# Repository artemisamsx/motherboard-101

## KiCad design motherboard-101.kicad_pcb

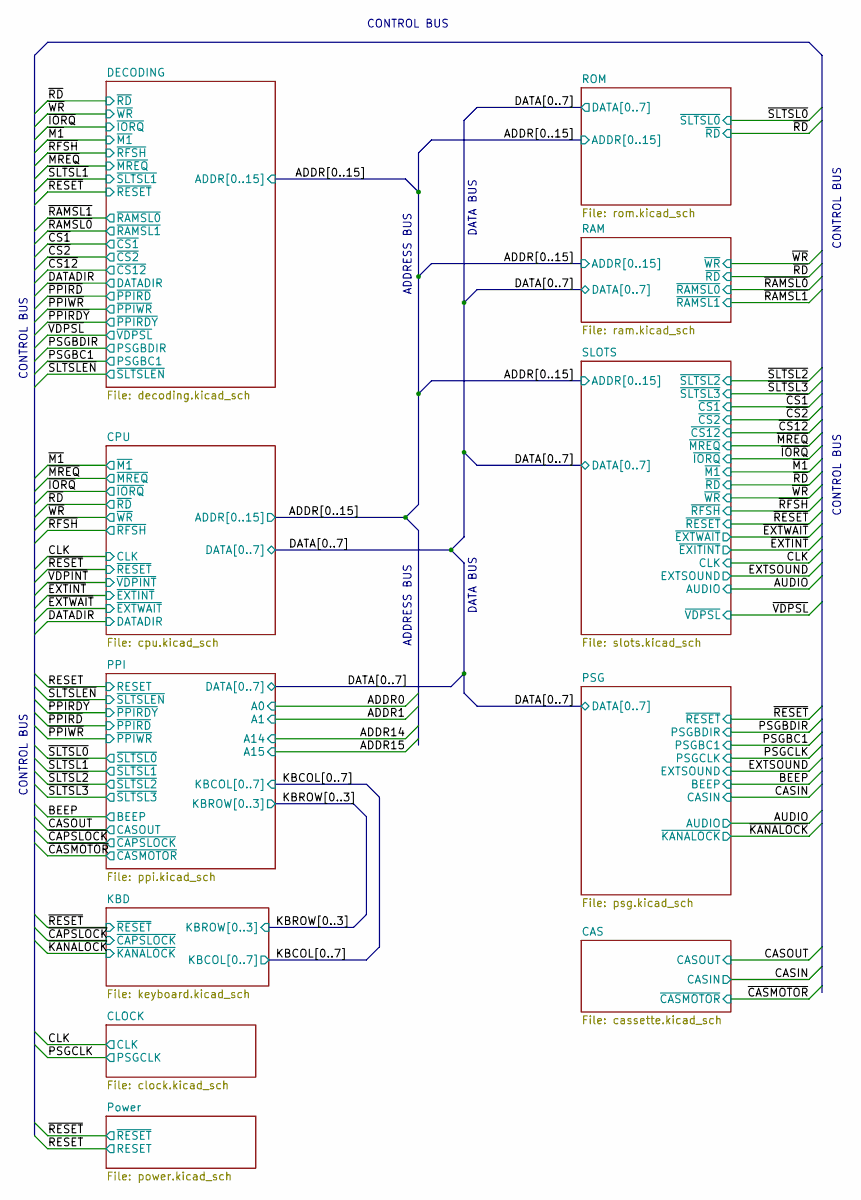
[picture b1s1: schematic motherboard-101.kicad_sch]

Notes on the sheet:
CONTROL BUS
ADDRESS BUS
DATA BUS

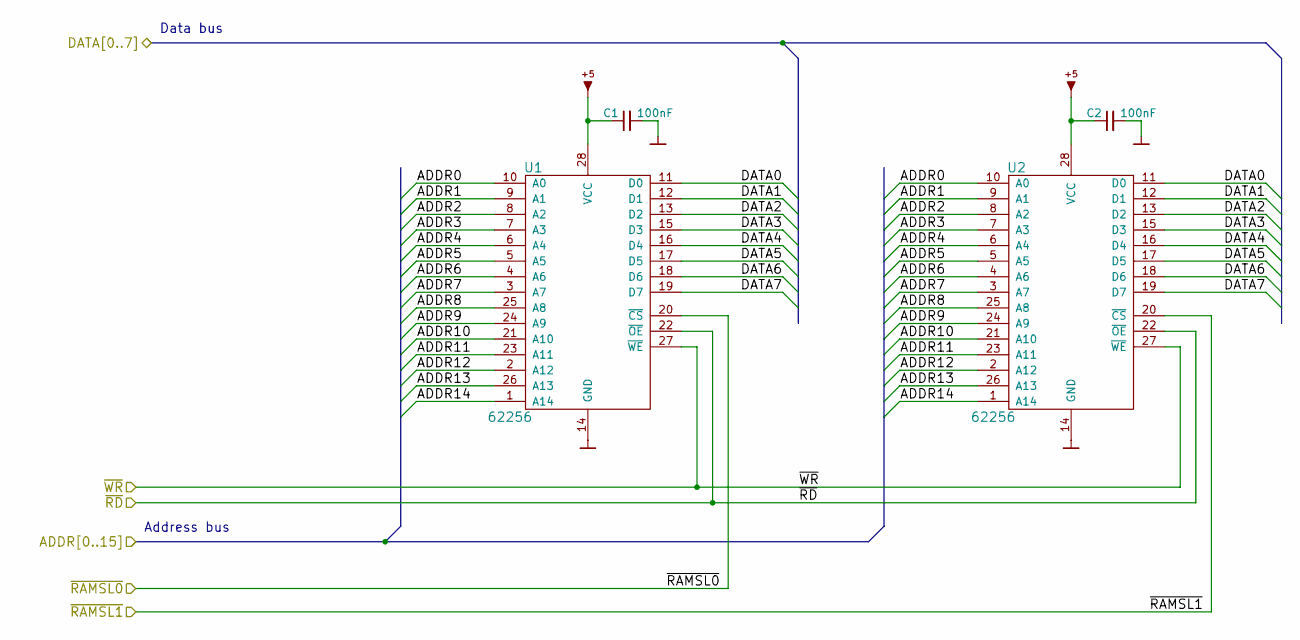
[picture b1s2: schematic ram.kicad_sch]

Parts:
C1, C2: 100nF; Disc_capacitor
U1, U2: 62256; DIP-28_600

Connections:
/ADDR0: U1.10 (A0), U2.10 (A0); also elsewhere on the board
/ADDR1: U1.9 (A1), U2.9 (A1); also elsewhere on the board
/ADDR14: U1.1 (A14), U2.1 (A14); also elsewhere on the board
/CPU/ADDR2: U1.8 (A2), U2.8 (A2); also elsewhere on the board
/CPU/ADDR3: U1.7 (A3), U2.7 (A3); also elsewhere on the board
/CPU/ADDR4: U1.6 (A4), U2.6 (A4); also elsewhere on the board
/CPU/ADDR5: U1.5 (A5), U2.5 (A5); also elsewhere on the board
/CPU/ADDR6: U1.4 (A6), U2.4 (A6); also elsewhere on the board
/CPU/ADDR7: U1.3 (A7), U2.3 (A7); also elsewhere on the board
/CPU/ADDR8: U1.25 (A8), U2.25 (A8); also elsewhere on the board
/CPU/ADDR9: U1.24 (A9), U2.24 (A9); also elsewhere on the board
/CPU/ADDR10: U1.21 (A10), U2.21 (A10); also elsewhere on the board
/CPU/ADDR11: U1.23 (A11), U2.23 (A11); also elsewhere on the board
/CPU/ADDR12: U1.2 (A12), U2.2 (A12); also elsewhere on the board
/CPU/ADDR13: U1.26 (A13), U2.26 (A13); also elsewhere on the board
/CPU/DATA0: U1.11 (D0), U2.11 (D0); also elsewhere on the board
/CPU/DATA1: U1.12 (D1), U2.12 (D1); also elsewhere on the board
/CPU/DATA2: U1.13 (D2), U2.13 (D2); also elsewhere on the board
/CPU/DATA3: U1.15 (D3), U2.15 (D3); also elsewhere on the board
/CPU/DATA4: U1.16 (D4), U2.16 (D4); also elsewhere on the board
/CPU/DATA5: U1.17 (D5), U2.17 (D5); also elsewhere on the board
/CPU/DATA6: U1.18 (D6), U2.18 (D6); also elsewhere on the board
/CPU/DATA7: U1.19 (D7), U2.19 (D7); also elsewhere on the board
/~RAMSL0: U1.20 (~CS); also elsewhere on the board
/~RAMSL1: U2.20 (~CS); also elsewhere on the board
/~RD: U1.22 (~OE), U2.22 (~OE); also elsewhere on the board
/~WR: U1.27 (~WE), U2.27 (~WE); also elsewhere on the board
GND: C1.2, C2.2, U1.14 (GND), U2.14 (GND); also elsewhere on the board
~: C1.1, C2.1, U1.28 (VCC), U2.28 (VCC); also elsewhere on the board

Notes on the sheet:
Data bus
Address bus

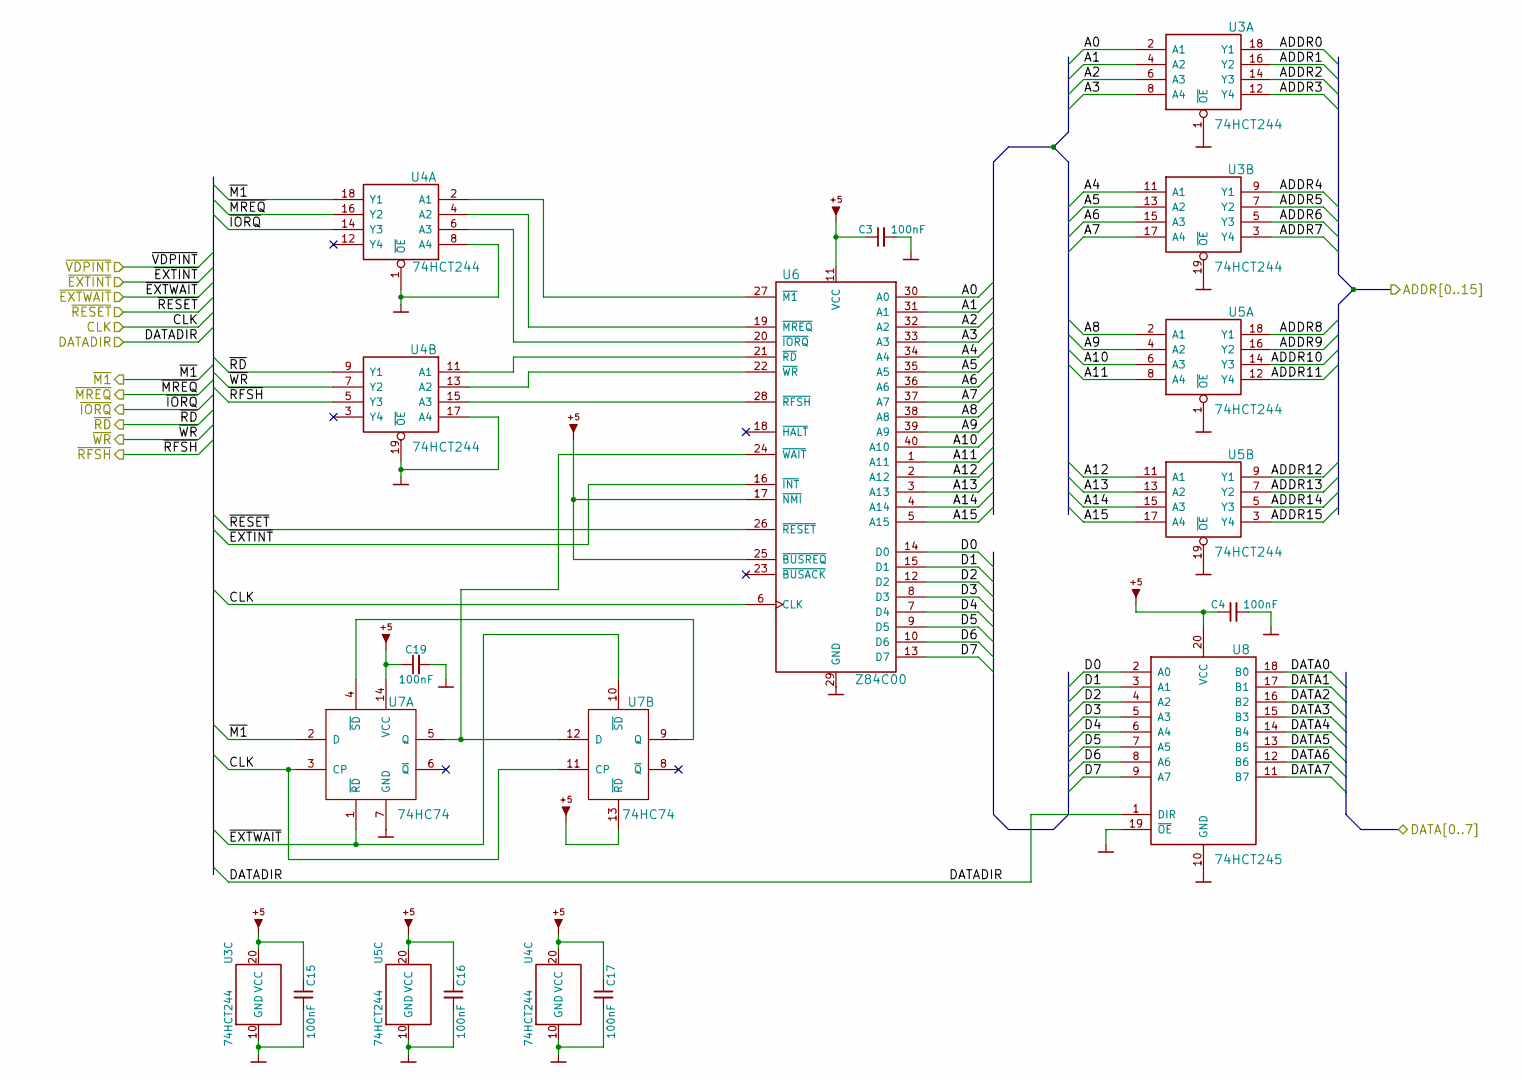
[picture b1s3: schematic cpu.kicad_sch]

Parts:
C3, C4, C15, C16, C17, C19: 100nF; Disc_capacitor
U3, U4, U5: 74HCT244; DIP-20_300
U6: Z84C00; DIP-40_600
U7: 74HC74; DIP-14_300
U8: 74HCT245; DIP-20_300

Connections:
/ADDR0: U3.18 (Y1); also elsewhere on the board
/ADDR1: U3.16 (Y2); also elsewhere on the board
/ADDR14: U5.5 (Y3); also elsewhere on the board
/ADDR15: U5.3 (Y4); also elsewhere on the board
/CLK: U6.6 (CLK), U7.3 (CP), U7.11 (CP); also elsewhere on the board
/CPU/A0: U3.2 (A1), U6.30 (A0)
/CPU/A1: U3.4 (A2), U6.31 (A1)
/CPU/A2: U3.6 (A3), U6.32 (A2)
/CPU/A3: U3.8 (A4), U6.33 (A3)
/CPU/A4: U3.11 (A1), U6.34 (A4)
/CPU/A5: U3.13 (A2), U6.35 (A5)
/CPU/A6: U3.15 (A3), U6.36 (A6)
/CPU/A7: U3.17 (A4), U6.37 (A7)
/CPU/A8: U5.2 (A1), U6.38 (A8)
/CPU/A9: U5.4 (A2), U6.39 (A9)
/CPU/A10: U5.6 (A3), U6.40 (A10)
/CPU/A11: U5.8 (A4), U6.1 (A11)
/CPU/A12: U5.11 (A1), U6.2 (A12)
/CPU/A13: U5.13 (A2), U6.3 (A13)
/CPU/A14: U5.15 (A3), U6.4 (A14)
/CPU/A15: U5.17 (A4), U6.5 (A15)
/CPU/ADDR2: U3.14 (Y3); also elsewhere on the board
/CPU/ADDR3: U3.12 (Y4); also elsewhere on the board
/CPU/ADDR4: U3.9 (Y1); also elsewhere on the board
/CPU/ADDR5: U3.7 (Y2); also elsewhere on the board
/CPU/ADDR6: U3.5 (Y3); also elsewhere on the board
/CPU/ADDR7: U3.3 (Y4); also elsewhere on the board
/CPU/ADDR8: U5.18 (Y1); also elsewhere on the board
/CPU/ADDR9: U5.16 (Y2); also elsewhere on the board
/CPU/ADDR10: U5.14 (Y3); also elsewhere on the board
/CPU/ADDR11: U5.12 (Y4); also elsewhere on the board
/CPU/ADDR12: U5.9 (Y1); also elsewhere on the board
/CPU/ADDR13: U5.7 (Y2); also elsewhere on the board
/CPU/D0: U6.14 (D0), U8.2 (A0)
/CPU/D1: U6.15 (D1), U8.3 (A1)
/CPU/D2: U6.12 (D2), U8.4 (A2)
/CPU/D3: U6.8 (D3), U8.5 (A3)
/CPU/D4: U6.7 (D4), U8.6 (A4)
/CPU/D5: U6.9 (D5), U8.7 (A5)
/CPU/D6: U6.10 (D6), U8.8 (A6)
/CPU/D7: U6.13 (D7), U8.9 (A7)
/CPU/DATA0: U8.18 (B0); also elsewhere on the board
/CPU/DATA1: U8.17 (B1); also elsewhere on the board
/CPU/DATA2: U8.16 (B2); also elsewhere on the board
/CPU/DATA3: U8.15 (B3); also elsewhere on the board
/CPU/DATA4: U8.14 (B4); also elsewhere on the board
/CPU/DATA5: U8.13 (B5); also elsewhere on the board
/CPU/DATA6: U8.12 (B6); also elsewhere on the board
/CPU/DATA7: U8.11 (B7); also elsewhere on the board
/DATADIR: U8.1 (DIR); also elsewhere on the board
/~EXTINT: U6.16 (~INT); also elsewhere on the board
/~EXTWAIT: U7.1 (~RD), U7.10 (~SD); also elsewhere on the board
/~IORQ: U4.14 (Y3); also elsewhere on the board
/~M1: U4.18 (Y1), U7.2 (D); also elsewhere on the board
/~MREQ: U4.16 (Y2); also elsewhere on the board
/~RD: U4.9 (Y1); also elsewhere on the board
/~RESET: U6.26 (~RESET); also elsewhere on the board
/~RFSH: U4.5 (Y3); also elsewhere on the board
/~WR: U4.7 (Y2); also elsewhere on the board
GND: C3.2, C4.2, C15.2, C16.2, C17.2, C19.2, U3.1 (~OE), U3.10 (GND), U3.19 (~OE), U4.1 (~OE), U4.8 (A4), U4.10 (GND), U4.17 (A4), U4.19 (~OE), U5.1 (~OE), U5.10 (GND), U5.19 (~OE), U6.29 (GND), U7.7 (GND), U8.10 (GND), U8.19 (~OE); also elsewhere on the board
unnamed: U4.2 (A1), U6.27 (~M1)
unnamed: U4.4 (A2), U6.19 (~MREQ)
unnamed: U4.6 (A3), U6.20 (~IORQ)
unnamed: U4.11 (A1), U6.21 (~RD)
unnamed: U4.13 (A2), U6.22 (~WR)
unnamed: U4.15 (A3), U6.28 (~RFSH)
unnamed: U6.24 (~WAIT), U7.5 (Q), U7.12 (D)
unnamed: U7.4 (~SD), U7.9 (Q)
~: C3.1, C4.1, C15.1, C16.1, C17.1, C19.1, U3.20 (VCC), U4.20 (VCC), U5.20 (VCC), U6.11 (VCC), U6.17 (~NMI), U6.25 (~BUSREQ), U7.13 (~RD), U7.14 (VCC), U8.20 (VCC); also elsewhere on the board

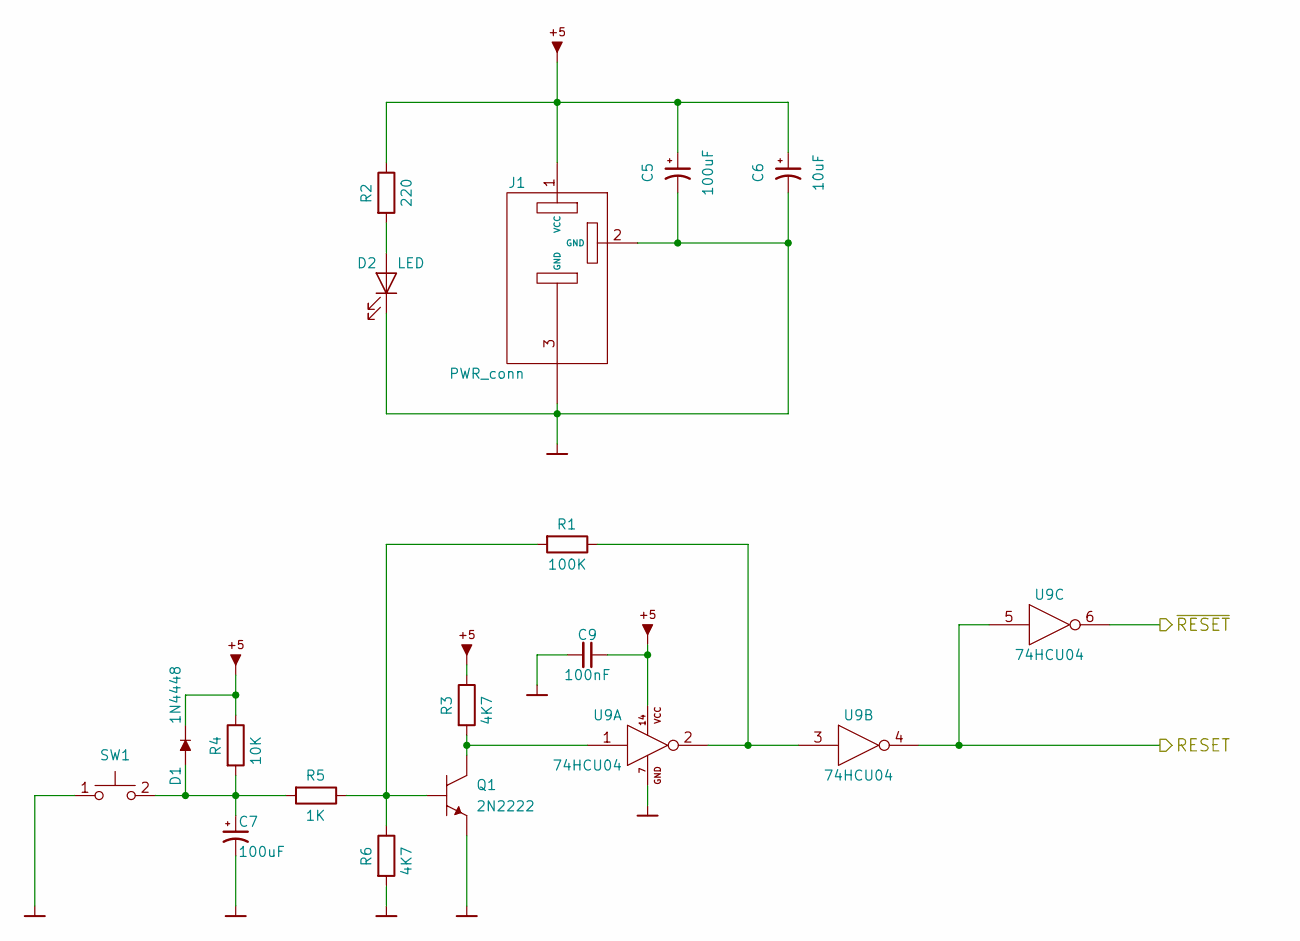
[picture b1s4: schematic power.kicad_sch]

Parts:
C5, C7: 100uF; Radial_capacitor
C6: 10uF; Radial_capacitor
C9: 100nF; Disc_capacitor
D1: 1N4448; Axial_diode
D2: LED
J1: PWR_conn; Jack_55_21
Q1: 2N2222; TO92
R1: 100K; Axial_resistor
R2: 220; Axial_resistor
R3, R6: 4K7; Axial_resistor
R4: 10K; Axial_resistor
R5: 1K; Axial_resistor
SW1: Push_button; Push_button_angled
U9: 74HCU04; DIP-14_300

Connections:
/RESET: U9.4, U9.5; also elsewhere on the board
/~RESET: U9.6; also elsewhere on the board
GND: C5.2, C6.2, C7.2, C9.2, D2.2 (K), J1.2 (GND), J1.3 (GND), Q1.3 (E), R6.2, SW1.1, U9.7 (GND); also elsewhere on the board
unnamed: C7.1, D1.1, R4.2, R5.2, SW1.2
unnamed: D2.1 (A), R2.2
unnamed: Q1.1 (1C), R3.2, U9.1
unnamed: Q1.2 (B), R1.2, R5.1, R6.1
unnamed: R1.1, U9.2, U9.3
~: C5.1, C6.1, C9.1, D1.2, J1.1 (VCC), R2.1, R3.1, R4.1, U9.14 (VCC); also elsewhere on the board

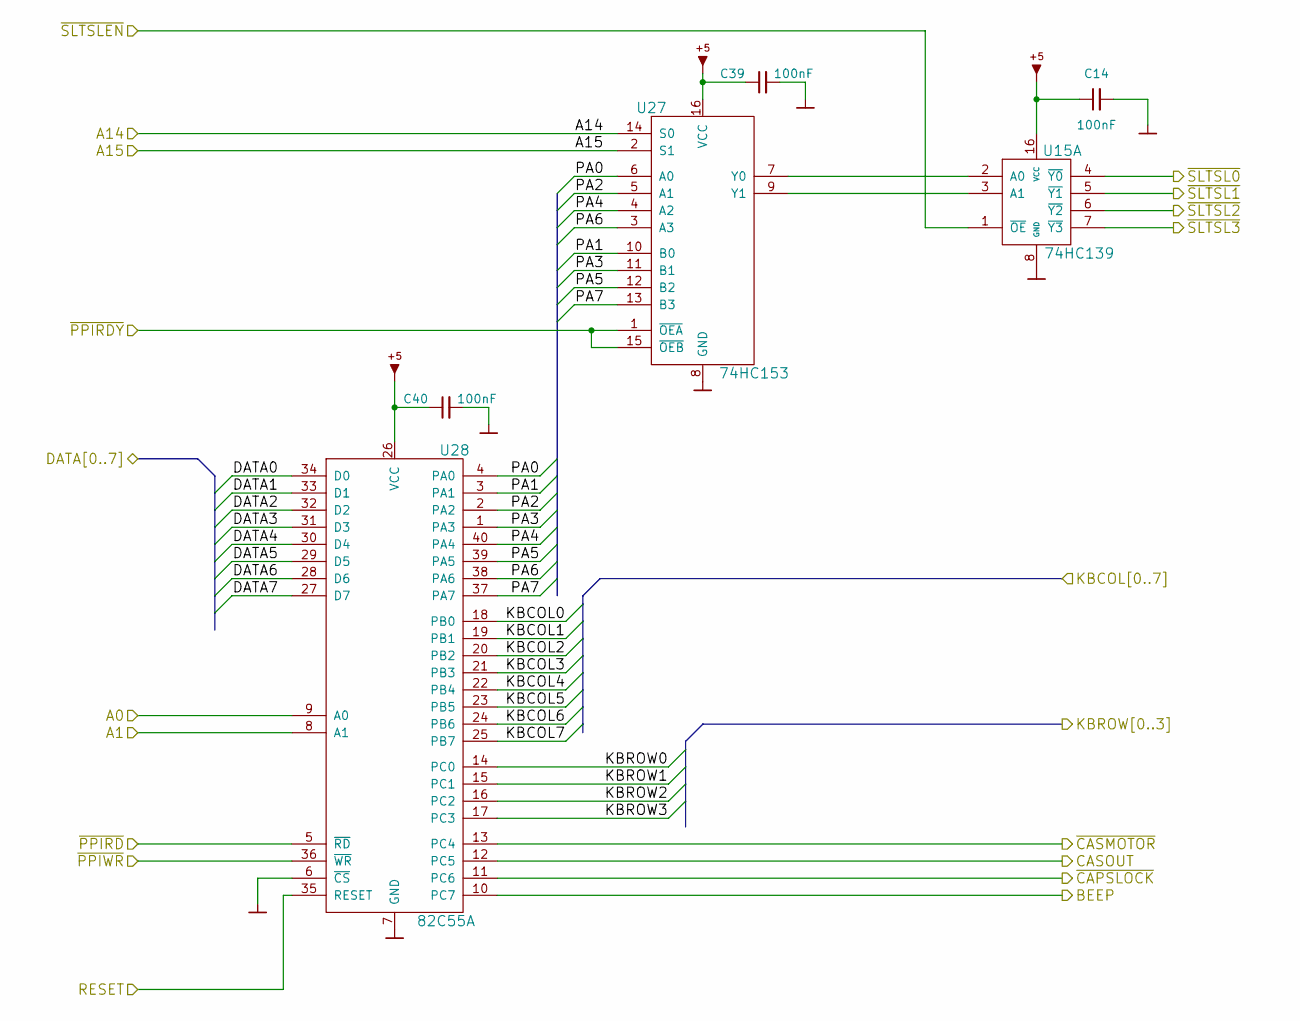
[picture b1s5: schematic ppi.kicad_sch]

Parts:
C14, C39, C40: 100nF; Disc_capacitor
U15: 74HC139; DIP-16_300
U27: 74HC153; DIP-16_300
U28: 82C55A; DIP-40_600

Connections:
/ADDR0: U28.9 (A0); also elsewhere on the board
/ADDR1: U28.8 (A1); also elsewhere on the board
/ADDR14: U27.14 (S0); also elsewhere on the board
/ADDR15: U27.2 (S1); also elsewhere on the board
/BEEP: U28.10 (PC7); also elsewhere on the board
/CASOUT: U28.12 (PC5); also elsewhere on the board
/CPU/DATA0: U28.34 (D0); also elsewhere on the board
/CPU/DATA1: U28.33 (D1); also elsewhere on the board
/CPU/DATA2: U28.32 (D2); also elsewhere on the board
/CPU/DATA3: U28.31 (D3); also elsewhere on the board
/CPU/DATA4: U28.30 (D4); also elsewhere on the board
/CPU/DATA5: U28.29 (D5); also elsewhere on the board
/CPU/DATA6: U28.28 (D6); also elsewhere on the board
/CPU/DATA7: U28.27 (D7); also elsewhere on the board
/KBD/KBCOL0: U28.18 (PB0); also elsewhere on the board
/KBD/KBCOL1: U28.19 (PB1); also elsewhere on the board
/KBD/KBCOL2: U28.20 (PB2); also elsewhere on the board
/KBD/KBCOL3: U28.21 (PB3); also elsewhere on the board
/KBD/KBCOL4: U28.22 (PB4); also elsewhere on the board
/KBD/KBCOL5: U28.23 (PB5); also elsewhere on the board
/KBD/KBCOL6: U28.24 (PB6); also elsewhere on the board
/KBD/KBCOL7: U28.25 (PB7); also elsewhere on the board
/KBD/KBROW0: U28.14 (PC0); also elsewhere on the board
/KBD/KBROW1: U28.15 (PC1); also elsewhere on the board
/KBD/KBROW2: U28.16 (PC2); also elsewhere on the board
/KBD/KBROW3: U28.17 (PC3); also elsewhere on the board
/PPI/PA0: U27.6 (A0), U28.4 (PA0)
/PPI/PA1: U27.10 (B0), U28.3 (PA1)
/PPI/PA2: U27.5 (A1), U28.2 (PA2)
/PPI/PA3: U27.11 (B1), U28.1 (PA3)
/PPI/PA4: U27.4 (A2), U28.40 (PA4)
/PPI/PA5: U27.12 (B2), U28.39 (PA5)
/PPI/PA6: U27.3 (A3), U28.38 (PA6)
/PPI/PA7: U27.13 (B3), U28.37 (PA7)
/RESET: U28.35 (RESET); also elsewhere on the board
/~CAPSLOCK: U28.11 (PC6); also elsewhere on the board
/~CASMOTOR: U28.13 (PC4); also elsewhere on the board
/~PPIRD: U28.5 (~RD); also elsewhere on the board
/~PPIRDY: U27.1 (~OEA), U27.15 (~OEB); also elsewhere on the board
/~PPIWR: U28.36 (~WR); also elsewhere on the board
/~SLTSL0: U15.4 (~Y0); also elsewhere on the board
/~SLTSL1: U15.5 (~Y1); also elsewhere on the board
/~SLTSL2: U15.6 (~Y2); also elsewhere on the board
/~SLTSL3: U15.7 (~Y3); also elsewhere on the board
/~SLTSLEN: U15.1 (~OE); also elsewhere on the board
GND: C14.2, C39.2, C40.2, U15.8 (GND), U27.8 (GND), U28.6 (~CS), U28.7 (GND); also elsewhere on the board
unnamed: U15.2 (A0), U27.7 (Y0)
unnamed: U15.3 (A1), U27.9 (Y1)
~: C14.1, C39.1, C40.1, U15.16 (VCC), U27.16 (VCC), U28.26 (VCC); also elsewhere on the board

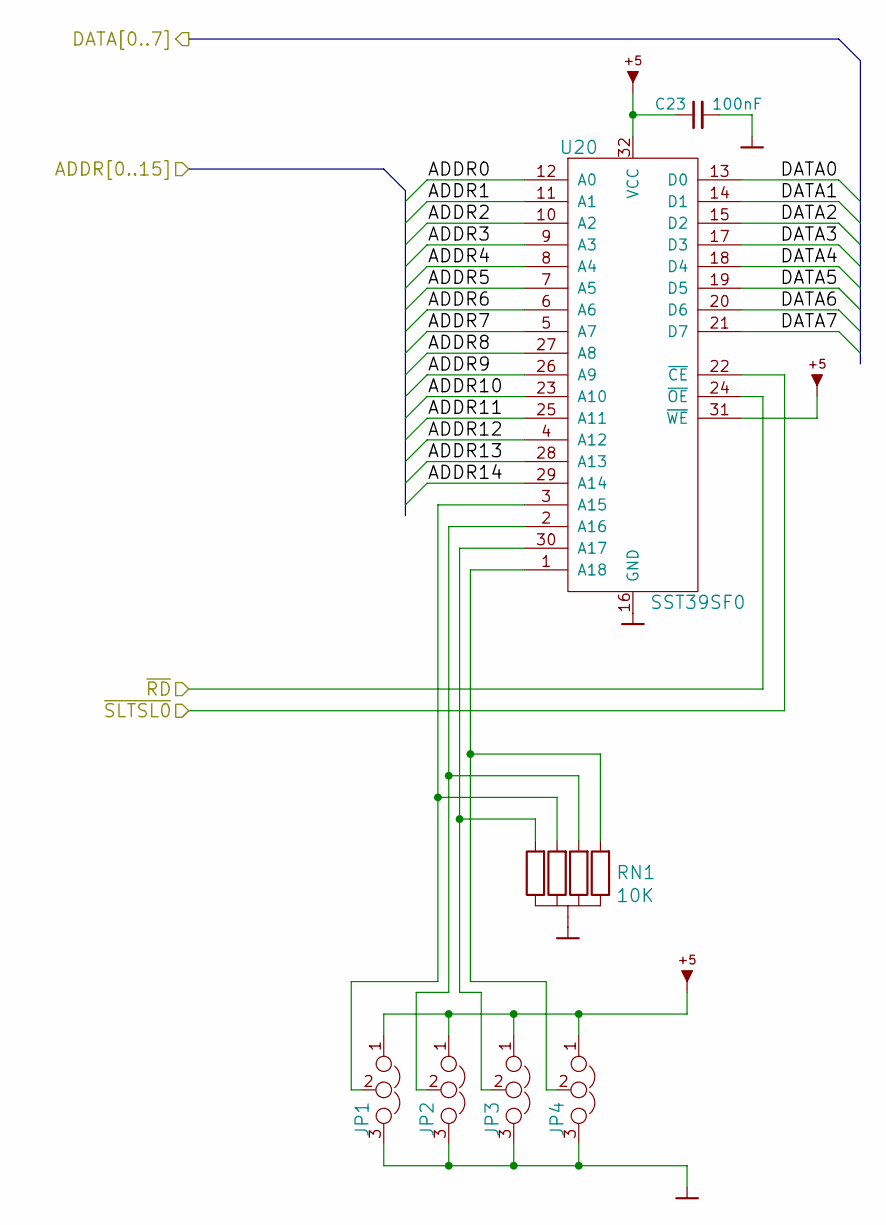
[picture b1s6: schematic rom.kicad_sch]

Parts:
C23: 100nF; Disc_capacitor
JP1, JP2, JP3, JP4: Jumper
RN1: 10K; RN4
U20: SST39SF0; DIP-32_600

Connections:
/ADDR0: U20.12 (A0); also elsewhere on the board
/ADDR1: U20.11 (A1); also elsewhere on the board
/ADDR14: U20.29 (A14); also elsewhere on the board
/CPU/ADDR2: U20.10 (A2); also elsewhere on the board
/CPU/ADDR3: U20.9 (A3); also elsewhere on the board
/CPU/ADDR4: U20.8 (A4); also elsewhere on the board
/CPU/ADDR5: U20.7 (A5); also elsewhere on the board
/CPU/ADDR6: U20.6 (A6); also elsewhere on the board
/CPU/ADDR7: U20.5 (A7); also elsewhere on the board
/CPU/ADDR8: U20.27 (A8); also elsewhere on the board
/CPU/ADDR9: U20.26 (A9); also elsewhere on the board
/CPU/ADDR10: U20.23 (A10); also elsewhere on the board
/CPU/ADDR11: U20.25 (A11); also elsewhere on the board
/CPU/ADDR12: U20.4 (A12); also elsewhere on the board
/CPU/ADDR13: U20.28 (A13); also elsewhere on the board
/CPU/DATA0: U20.13 (D0); also elsewhere on the board
/CPU/DATA1: U20.14 (D1); also elsewhere on the board
/CPU/DATA2: U20.15 (D2); also elsewhere on the board
/CPU/DATA3: U20.17 (D3); also elsewhere on the board
/CPU/DATA4: U20.18 (D4); also elsewhere on the board
/CPU/DATA5: U20.19 (D5); also elsewhere on the board
/CPU/DATA6: U20.20 (D6); also elsewhere on the board
/CPU/DATA7: U20.21 (D7); also elsewhere on the board
/~RD: U20.24 (~OE); also elsewhere on the board
/~SLTSL0: U20.22 (~CE); also elsewhere on the board
GND: C23.2, JP1.3, JP2.3, JP3.3, JP4.3, RN1.1, U20.16 (GND); also elsewhere on the board
unnamed: JP1.2, RN1.4, U20.3 (A15)
unnamed: JP2.2, RN1.3, U20.2 (A16)
unnamed: JP3.2, RN1.5, U20.30 (A17)
unnamed: JP4.2, RN1.2, U20.1 (A18)
~: C23.1, JP1.1, JP2.1, JP3.1, JP4.1, U20.31 (~WE), U20.32 (VCC); also elsewhere on the board

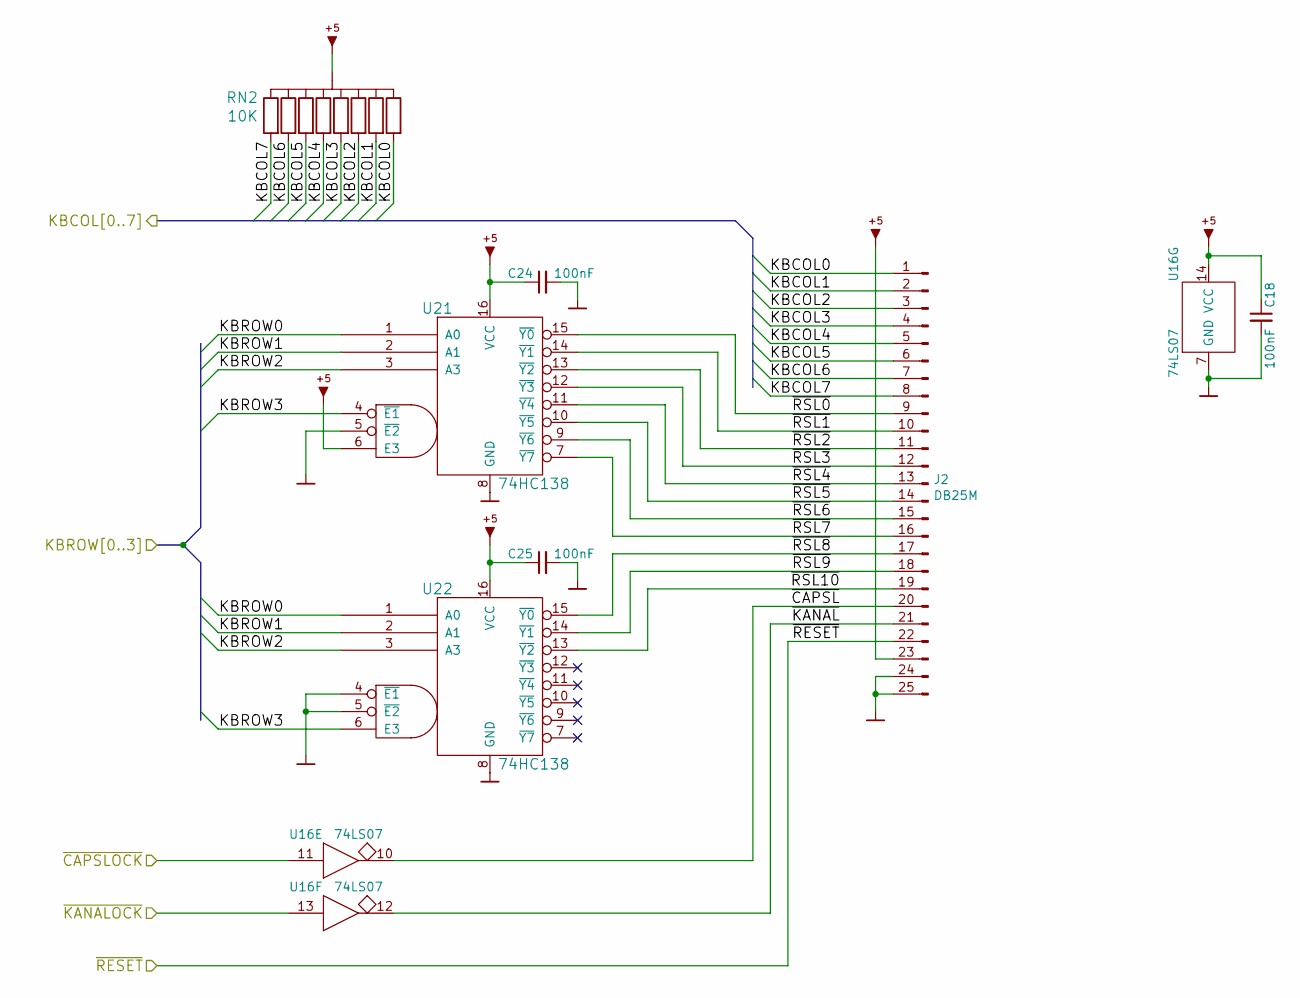
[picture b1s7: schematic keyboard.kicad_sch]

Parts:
C18, C24, C25: 100nF; Disc_capacitor
J2: DB25M
RN2: 10K; RN8
U16: 74LS07; DIP-14_300
U21, U22: 74HC138; DIP-16_300

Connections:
/KBD/KBCOL0: J2.1, RN2.2; also elsewhere on the board
/KBD/KBCOL1: J2.2, RN2.3; also elsewhere on the board
/KBD/KBCOL2: J2.3, RN2.4; also elsewhere on the board
/KBD/KBCOL3: J2.4, RN2.5; also elsewhere on the board
/KBD/KBCOL4: J2.5, RN2.6; also elsewhere on the board
/KBD/KBCOL5: J2.6, RN2.7; also elsewhere on the board
/KBD/KBCOL6: J2.7, RN2.8; also elsewhere on the board
/KBD/KBCOL7: J2.8, RN2.9; also elsewhere on the board
/KBD/KBROW0: U21.1 (A0), U22.1 (A0); also elsewhere on the board
/KBD/KBROW1: U21.2 (A1), U22.2 (A1); also elsewhere on the board
/KBD/KBROW2: U21.3 (A3), U22.3 (A3); also elsewhere on the board
/KBD/KBROW3: U21.4 (~E1), U22.6 (E3); also elsewhere on the board
/KBD/~CAPSL: J2.20, U16.10
/KBD/~KANAL: J2.21, U16.12
/KBD/~RSL0: J2.9, U21.15 (~Y0)
/KBD/~RSL1: J2.10, U21.14 (~Y1)
/KBD/~RSL2: J2.11, U21.13 (~Y2)
/KBD/~RSL3: J2.12, U21.12 (~Y3)
/KBD/~RSL4: J2.13, U21.11 (~Y4)
/KBD/~RSL5: J2.14, U21.10 (~Y5)
/KBD/~RSL6: J2.15, U21.9 (~Y6)
/KBD/~RSL7: J2.16, U21.7 (~Y7)
/KBD/~RSL8: J2.17, U22.15 (~Y0)
/KBD/~RSL9: J2.18, U22.14 (~Y1)
/KBD/~RSL10: J2.19, U22.13 (~Y2)
/~CAPSLOCK: U16.11; also elsewhere on the board
/~KANALOCK: U16.13; also elsewhere on the board
/~RESET: J2.22; also elsewhere on the board
GND: C18.2, C24.2, C25.2, J2.24, J2.25, U16.7 (GND), U21.5 (~E2), U21.8 (GND), U22.4 (~E1), U22.5 (~E2), U22.8 (GND); also elsewhere on the board
~: C18.1, C24.1, C25.1, J2.23, RN2.1, U16.14 (VCC), U21.6 (E3), U21.16 (VCC), U22.16 (VCC); also elsewhere on the board

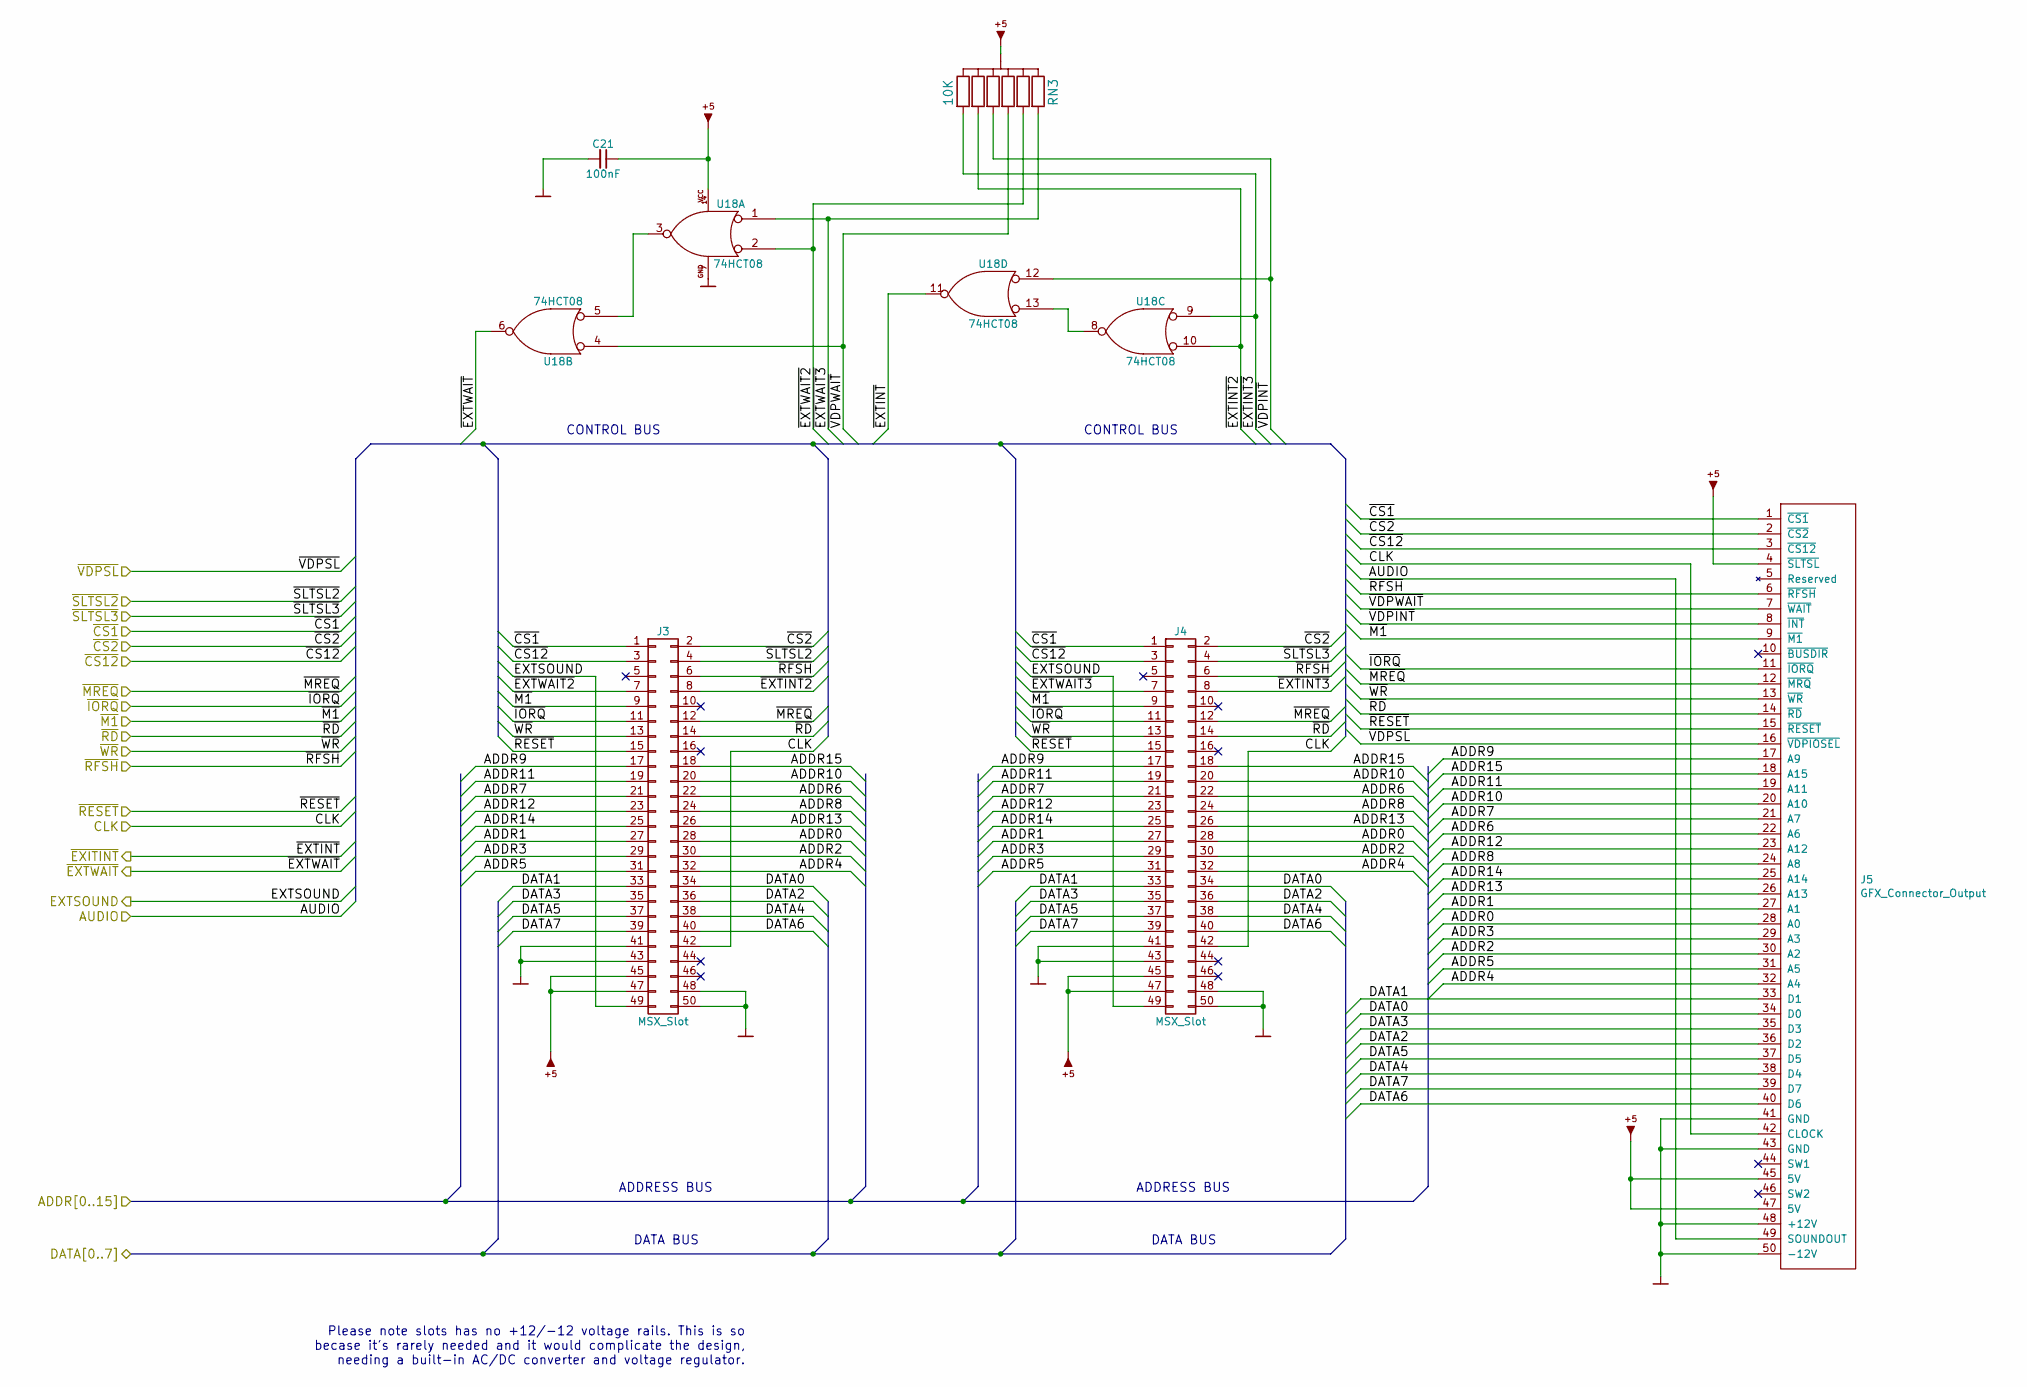
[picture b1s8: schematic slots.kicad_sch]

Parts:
C21: 100nF; Disc_capacitor
J3, J4: MSX_Slot; Slot_conn
J5: GFX_Connector_Output; GFX_conn
RN3: 10K; RN6
U18: 74HCT08; DIP-14_300

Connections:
/ADDR0: J3.28, J4.28, J5.28 (A0); also elsewhere on the board
/ADDR1: J3.27, J4.27, J5.27 (A1); also elsewhere on the board
/ADDR14: J3.25, J4.25, J5.25 (A14); also elsewhere on the board
/ADDR15: J3.18, J4.18, J5.18 (A15); also elsewhere on the board
/AUDIO: J5.49 (SOUNDOUT); also elsewhere on the board
/CLK: J3.42, J4.42, J5.42 (CLOCK); also elsewhere on the board
/CPU/ADDR2: J3.30, J4.30, J5.30 (A2); also elsewhere on the board
/CPU/ADDR3: J3.29, J4.29, J5.29 (A3); also elsewhere on the board
/CPU/ADDR4: J3.32, J4.32, J5.32 (A4); also elsewhere on the board
/CPU/ADDR5: J3.31, J4.31, J5.31 (A5); also elsewhere on the board
/CPU/ADDR6: J3.22, J4.22, J5.22 (A6); also elsewhere on the board
/CPU/ADDR7: J3.21, J4.21, J5.21 (A7); also elsewhere on the board
/CPU/ADDR8: J3.24, J4.24, J5.24 (A8); also elsewhere on the board
/CPU/ADDR9: J3.17, J4.17, J5.17 (A9); also elsewhere on the board
/CPU/ADDR10: J3.20, J4.20, J5.20 (A10); also elsewhere on the board
/CPU/ADDR11: J3.19, J4.19, J5.19 (A11); also elsewhere on the board
/CPU/ADDR12: J3.23, J4.23, J5.23 (A12); also elsewhere on the board
/CPU/ADDR13: J3.26, J4.26, J5.26 (A13); also elsewhere on the board
/CPU/DATA0: J3.34, J4.34, J5.34 (D0); also elsewhere on the board
/CPU/DATA1: J3.33, J4.33, J5.33 (D1); also elsewhere on the board
/CPU/DATA2: J3.36, J4.36, J5.36 (D2); also elsewhere on the board
/CPU/DATA3: J3.35, J4.35, J5.35 (D3); also elsewhere on the board
/CPU/DATA4: J3.38, J4.38, J5.38 (D4); also elsewhere on the board
/CPU/DATA5: J3.37, J4.37, J5.37 (D5); also elsewhere on the board
/CPU/DATA6: J3.40, J4.40, J5.40 (D6); also elsewhere on the board
/CPU/DATA7: J3.39, J4.39, J5.39 (D7); also elsewhere on the board
/EXTSOUND: J3.49, J4.49; also elsewhere on the board
/SLOTS/~EXTINT2: J3.8, RN3.3, U18.10
/SLOTS/~EXTINT3: J4.8, RN3.2, U18.9
/SLOTS/~EXTWAIT2: J3.7, RN3.6, U18.2
/SLOTS/~EXTWAIT3: J4.7, RN3.7, U18.1
/SLOTS/~VDPINT: J5.8 (~INT), RN3.4, U18.12
/SLOTS/~VDPWAIT: J5.7 (~WAIT), RN3.5, U18.4
/~CS1: J3.1, J4.1, J5.1 (~CS1); also elsewhere on the board
/~CS2: J3.2, J4.2, J5.2 (~CS2); also elsewhere on the board
/~CS12: J3.3, J4.3, J5.3 (~CS12); also elsewhere on the board
/~EXTINT: U18.11; also elsewhere on the board
/~EXTWAIT: U18.6; also elsewhere on the board
/~IORQ: J3.11, J4.11, J5.11 (~IORQ); also elsewhere on the board
/~M1: J3.9, J4.9, J5.9 (~M1); also elsewhere on the board
/~MREQ: J3.12, J4.12, J5.12 (~MRQ); also elsewhere on the board
/~RD: J3.14, J4.14, J5.14 (~RD); also elsewhere on the board
/~RESET: J3.15, J4.15, J5.15 (~RESET); also elsewhere on the board
/~RFSH: J3.6, J4.6, J5.6 (~RFSH); also elsewhere on the board
/~SLTSL2: J3.4; also elsewhere on the board
/~SLTSL3: J4.4; also elsewhere on the board
/~VDPSL: J5.16 (~VDPIOSEL); also elsewhere on the board
/~WR: J3.13, J4.13, J5.13 (~WR); also elsewhere on the board
GND: C21.2, J3.41, J3.43, J3.48, J3.50, J4.41, J4.43, J4.48, J4.50, J5.41 (GND), J5.43 (GND), J5.48 (+12V), J5.50 (-12V), U18.7 (GND); also elsewhere on the board
unnamed: U18.3, U18.5
unnamed: U18.8, U18.13
~: C21.1, J3.45, J3.47, J4.45, J4.47, J5.4 (~SLTSL), J5.45 (5V), J5.47 (5V), RN3.1, U18.14 (VCC); also elsewhere on the board

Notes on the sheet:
ADDRESS BUS
DATA BUS
CONTROL BUS
Please note slots has no +12/-12 voltage rails. This is so becase it's rarely needed and it would complicate the design, needing a built-in AC/DC converter and voltage regulator.

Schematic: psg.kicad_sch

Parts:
C26, C27, C28: 100nF; Disc_capacitor
C29, C30, C31: 10u; Radial_capacitor
J6, J7: CONN_JOY; Joystick_conn
R7, R9: 10K; Axial_resistor
R8: 470; Axial_resistor
R10: 20k; Axial_resistor
R11: 4k7; Axial_resistor
R12: 2k7; Axial_resistor
RN4: 10K; RN8
RN5: 10K; RN4
U14: 74HC08; DIP-14_300
U16: 74LS07; DIP-14_300
U23, U25: 74HC157; DIP-16_300
U24: AY-3-8910; DIP-40_600

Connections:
/AUDIO: R10.2, R11.2, R12.2; also elsewhere on the board
/BEEP: C29.1; also elsewhere on the board
/CASIN: U24.14 (IOA7); also elsewhere on the board
/CPU/DATA0: U24.37 (DA0); also elsewhere on the board
/CPU/DATA1: U24.36 (DA1); also elsewhere on the board
/CPU/DATA2: U24.35 (DA2); also elsewhere on the board
/CPU/DATA3: U24.34 (DA3); also elsewhere on the board
/CPU/DATA4: U24.33 (DA4); also elsewhere on the board
/CPU/DATA5: U24.32 (DA5); also elsewhere on the board
/CPU/DATA6: U24.31 (DA6); also elsewhere on the board
/CPU/DATA7: U24.30 (DA7); also elsewhere on the board
/EXTSOUND: C30.1; also elsewhere on the board
/PSG/IOA0: U23.4 (Y0), U24.21 (IOA0)
/PSG/IOA1: U23.7 (Y1), U24.20 (IOA1)
/PSG/IOA2: U23.9 (Y2), U24.19 (IOA2)
/PSG/IOA3: U23.12 (Y3), U24.18 (IOA3)
/PSG/IOA4: U24.17 (IOA4), U25.4 (Y0)
/PSG/IOA5: U24.16 (IOA5), U25.7 (Y1)
/PSG/IOB0: U16.1, U24.13 (IOB0)
/PSG/IOB1: U16.3, U24.12 (IOB1)
/PSG/IOB2: U16.5, U24.11 (IOB2)
/PSG/IOB3: U16.9, U24.10 (IOB3)
/PSG/IOB4: J6.8, U24.9 (IOB4)
/PSG/IOB5: J7.8, U24.8 (IOB5)
/PSG/IOB6: U23.1 (S), U24.7 (IOB6), U25.1 (S)
/PSG/JOYA1: J6.1 (UP), RN4.9, U23.2 (A0)
/PSG/JOYA2: J6.2 (DOWN), RN4.8, U23.5 (A1)
/PSG/JOYA3: J6.3 (LEFT), RN4.7, U23.11 (A2)
/PSG/JOYA4: J6.4 (RIGHT), RN4.6, U23.14 (A3)
/PSG/JOYA6: J6.6 (TRIG1), RN5.5, U16.8, U25.2 (A0)
/PSG/JOYA7: J6.7 (TRIG2), RN5.4, U16.6, U25.5 (A1)
/PSG/JOYB1: J7.1 (UP), RN4.5, U23.3 (B0)
/PSG/JOYB2: J7.2 (DOWN), RN4.4, U23.6 (B1)
/PSG/JOYB3: J7.3 (LEFT), RN4.3, U23.10 (B2)
/PSG/JOYB4: J7.4 (RIGHT), RN4.2, U23.13 (B3)
/PSG/JOYB6: J7.6 (TRIG1), RN5.3, U16.4, U25.3 (B0)
/PSG/JOYB7: J7.7 (TRIG2), RN5.2, U16.2, U25.6 (B1)
/PSGBC1: U24.29 (BC1); also elsewhere on the board
/PSGBDIR: U24.27 (BDIR); also elsewhere on the board
/PSGCLK: U24.22 (CLK); also elsewhere on the board
/~KANALOCK: R9.1, U24.6 (IOB7); also elsewhere on the board
/~RESET: U24.23 (~RESET); also elsewhere on the board
GND: C26.2, C27.2, C28.2, J6.9 (GND), J7.9 (GND), R8.2, R9.2, U14.7 (GND), U14.12, U14.13, U23.8 (GND), U23.15 (~E), U24.1 (GND), U24.24 (~A9), U25.8 (GND), U25.10 (B2), U25.11 (A2), U25.13 (B3), U25.14 (A3), U25.15 (~E); also elsewhere on the board
unnamed: C29.2, R10.1
unnamed: C30.2, R11.1
unnamed: C31.1, R8.1, U24.3 (B), U24.4 (A), U24.38 (C)
unnamed: C31.2, R12.1
unnamed: R7.2, U24.15 (IOA6)
~: C26.1, C27.1, C28.1, J6.5 (VCC), J7.5 (VCC), R7.1, RN4.1, RN5.1, U14.14 (VCC), U23.16 (VCC), U24.25 (A8), U24.28 (BC2), U24.40 (VCC), U25.16 (VCC); also elsewhere on the board

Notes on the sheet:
This just mixes the three sound sources into a single line without amplifying. This should provide a reasonably good gain for output. Otherwise, a LM386 amplifier IC should be used instead.

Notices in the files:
motherboard-101.kicad_pcb:
Copyright (c) 2018, 2019 Alvaro Polo
